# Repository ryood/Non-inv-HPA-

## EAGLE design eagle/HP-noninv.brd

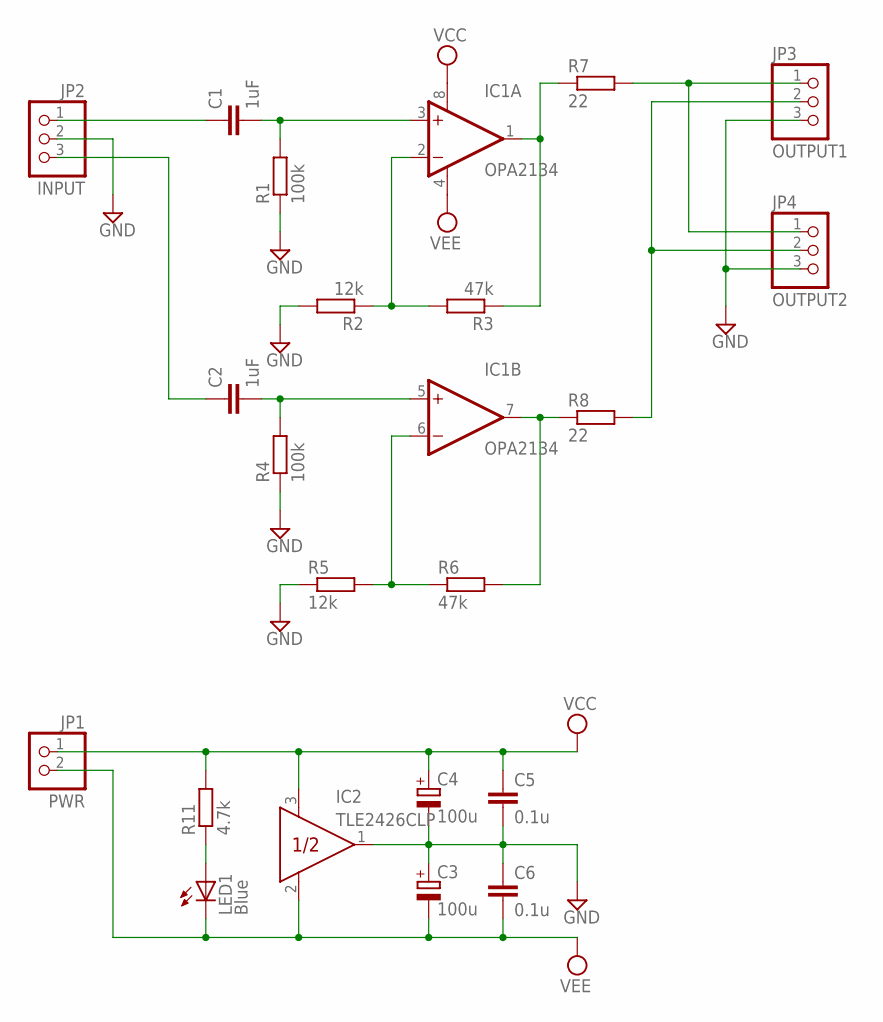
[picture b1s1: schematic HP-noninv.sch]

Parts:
C1, C2: 1uF; C050-050X075
C3, C4: 100u; TT5D6L
C5: 0.1u; C025-024X044
C6: 0.1u; C050-024X044
IC1: OPA2134; DIL08
IC2: TLE2426CLP; TO226AA
JP1: PWR; 1X02
JP2: INPUT; 1X03
JP3: OUTPUT1; 1X03
JP4: OUTPUT2; 1X03
LED1: Blue; LED3MM
R1, R4: 100k; 0207/7
R2, R5: 12k; 0207/7
R3, R6: 47k; 0207/7
R7, R8: 22; 0207/7
R11: 4.7k; 0207/7

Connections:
GND: C3.+, C4.-, C5.2, C6.1, IC2.1 (OUT), JP2.2, JP3.3, JP4.3, R1.1, R2.2, R4.1, R5.1
unnamed: C1.1, JP2.1
unnamed: IC1.1 (OUT), R3.1, R7.1
unnamed: C2.1, JP2.3
unnamed: IC1.7 (OUT), R6.2, R8.1
unnamed: C2.2, IC1.5 (+IN), R4.2
unnamed: C1.2, IC1.3 (+IN), R1.2
unnamed: IC1.2 (-IN), R2.1, R3.2
unnamed: JP3.1, JP4.1, R7.2
unnamed: IC1.6 (-IN), R5.2, R6.1
unnamed: JP3.2, JP4.2, R8.2
unnamed: LED1.A, R11.1
VCC: C4.+, C5.1, IC1.8 (V+), IC2.3 (IN), JP1.1, R11.2
VEE: C3.-, C6.2, IC1.4 (V-), IC2.2 (COM), JP1.2, LED1.K (C)

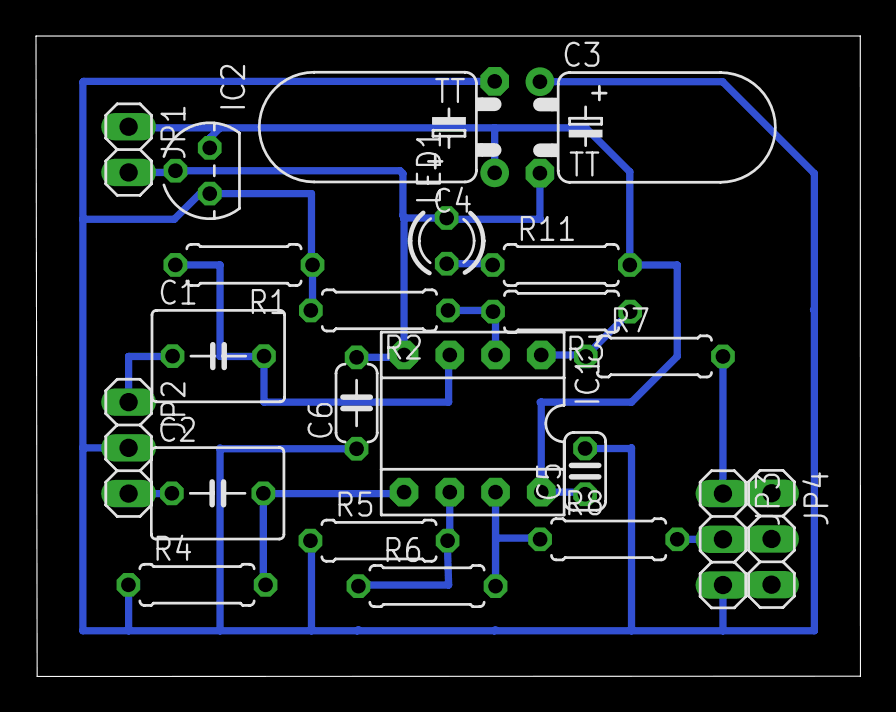
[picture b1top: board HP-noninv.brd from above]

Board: 2 copper layers, 45.8 x 35.6 mm, 22 parts (0 on the bottom side), 14 nets.

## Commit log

2015-12-19 保護抵抗追加
2015-12-19 ケミコンを倒して配置
2015-12-21 積セラの配置を変更
2015-12-22 Hardware完成
